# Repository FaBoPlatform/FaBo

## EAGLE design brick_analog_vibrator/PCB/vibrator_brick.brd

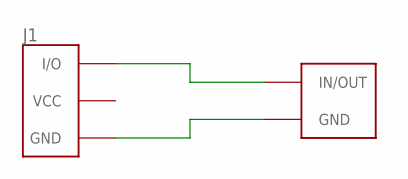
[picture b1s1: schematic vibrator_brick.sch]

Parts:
J1: BRICK_3PIN
U$1: VIBRATOR-LA3R5-480H1

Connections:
GND: J1.GND, U$1.P$2 (GND)
unnamed: J1.IN/OUT (I/O), U$1.P$1 (IN/OUT)

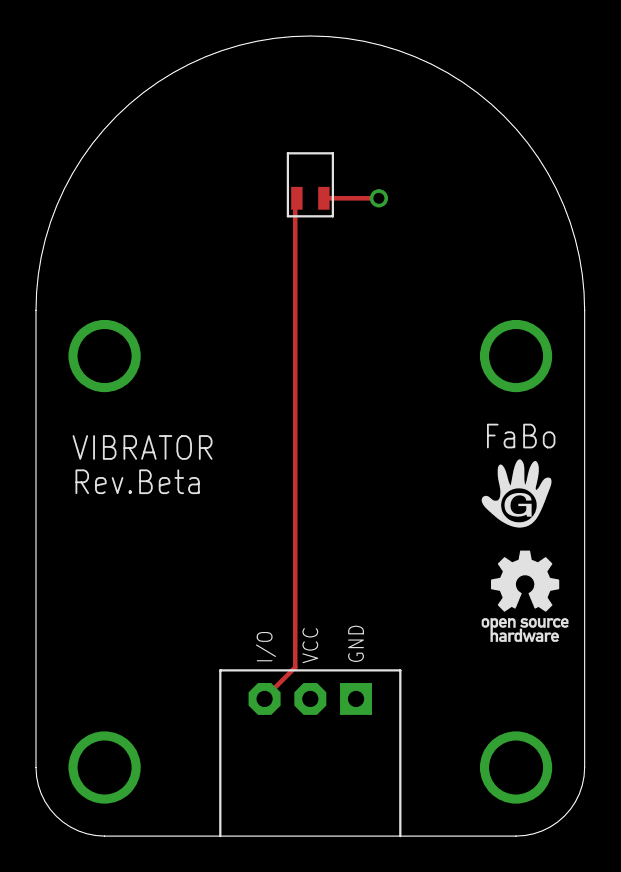
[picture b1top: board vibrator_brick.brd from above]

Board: 2 copper layers, 30.5 x 44.5 mm, 4 parts (0 on the bottom side), 2 nets.

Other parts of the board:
U$2: LOGO_GCLUE_M
U$4: LOGO_OSHW_T_M

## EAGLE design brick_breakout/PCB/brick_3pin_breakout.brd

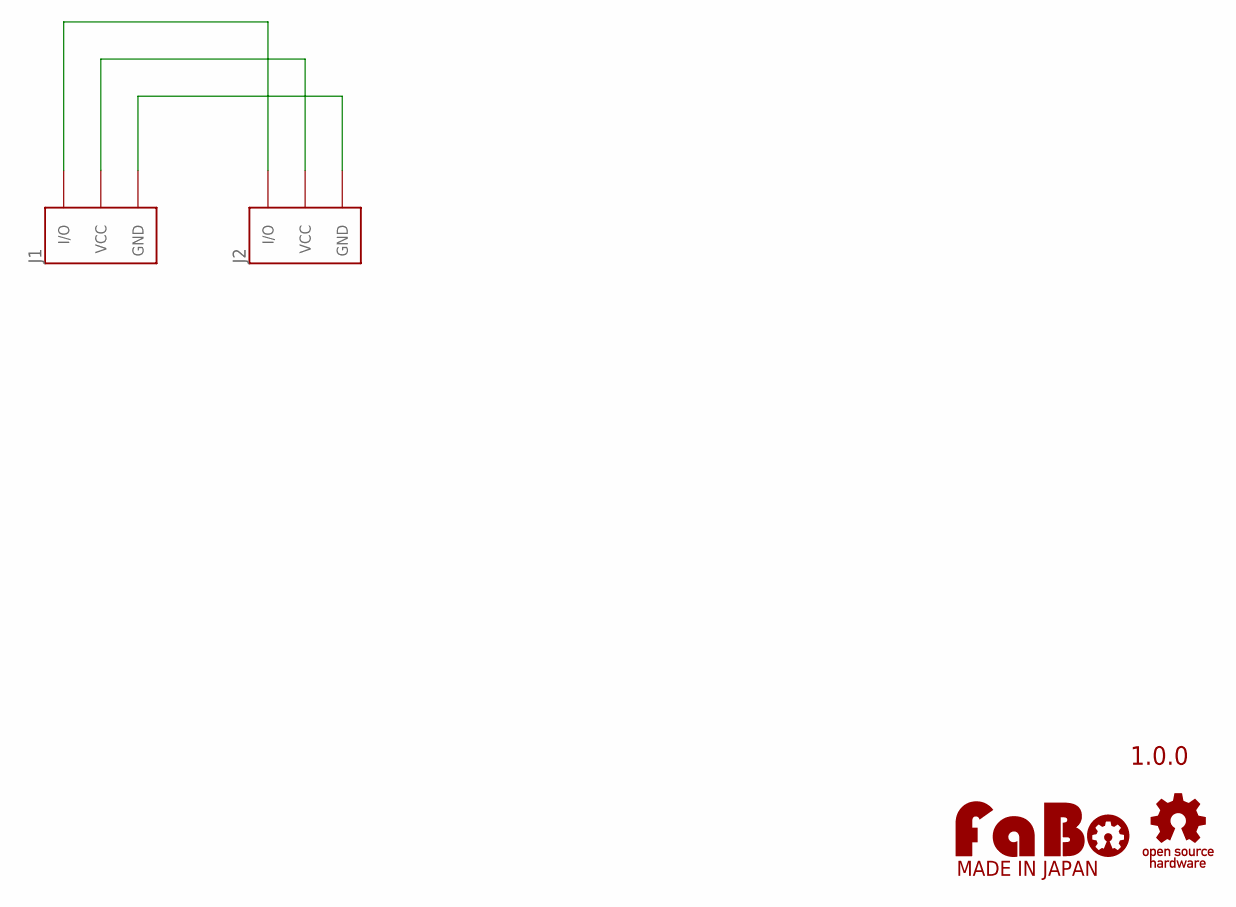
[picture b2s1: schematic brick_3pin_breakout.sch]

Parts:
J1: FABO_BRICK_3PIN-BREAKOUT; FABO_BRICK_3PIN_BREAKOUT
J2: FABO_BRICK_3PIN-CONNECTOR; FABO_BRICK_3PIN_CONNECTOR
U$2: LOGO_FABO-M_BOTTOM; LOGO_FABO_M_BOTTOM
U$3: LOGO_OSHW-T_M_BOTTOM; LOGO_OSHW_T_M_BOTTOM

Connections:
GND: J1.GND, J2.GND
IO: J1.IN/OUT (I/O), J2.IN/OUT (I/O)
VCC: J1.VCC, J2.VCC

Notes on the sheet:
1.0.0

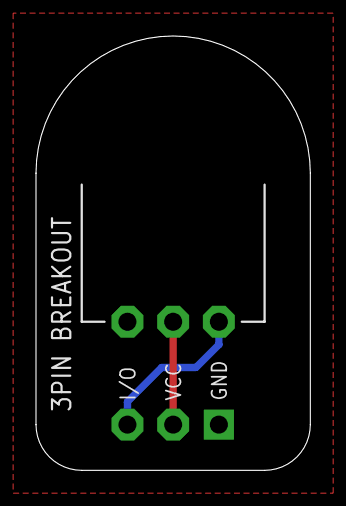
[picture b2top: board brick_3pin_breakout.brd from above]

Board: 2 copper layers, 15.2 x 24.1 mm, 4 parts (0 on the bottom side), 3 nets.

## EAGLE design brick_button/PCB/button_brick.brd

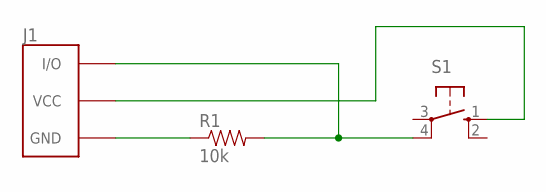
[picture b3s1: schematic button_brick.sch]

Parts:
J1: BRICK_3PIN
R1: 10k; AXIAL-0.4
S1: Button; B3F-10XX

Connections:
GND: J1.GND, R1.P$1 (1)
unnamed: J1.VCC, S1.1 (S)
unnamed: J1.IN/OUT (I/O), R1.P$2 (2), S1.4 (P1)

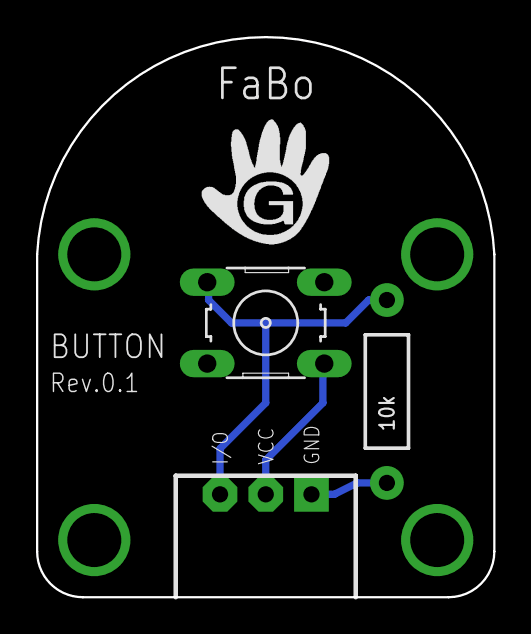
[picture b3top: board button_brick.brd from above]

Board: 2 copper layers, 25.4 x 31.1 mm, 3 parts (0 on the bottom side), 3 nets.

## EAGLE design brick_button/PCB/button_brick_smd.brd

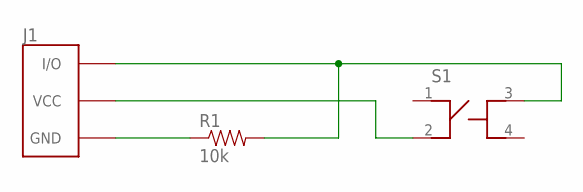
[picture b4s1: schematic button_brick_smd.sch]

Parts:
J1: BRICK_3PIN
R1: 10k; 0603-RES
S1: SWITCH-LS6J2M-T

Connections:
GND: J1.GND, R1.1
unnamed: J1.VCC, S1.2
unnamed: J1.IN/OUT (I/O), R1.2, S1.3

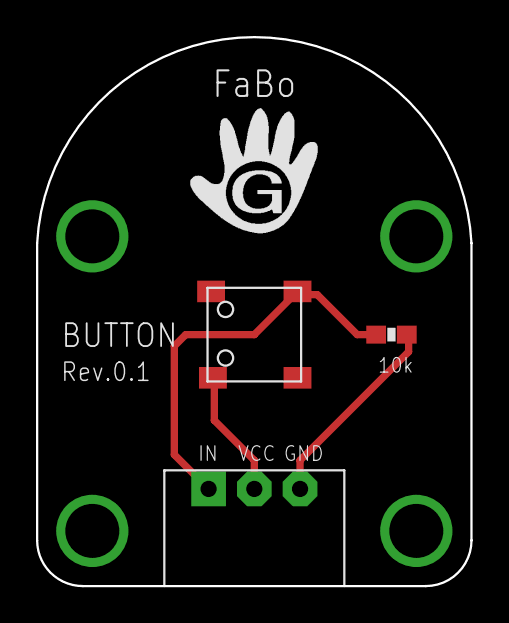
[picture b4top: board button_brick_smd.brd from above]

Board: 2 copper layers, 24.1 x 30.5 mm, 3 parts (0 on the bottom side), 3 nets.

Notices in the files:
parts and their libraries:
FaBo-Template: Released under the Creative Commons Attribution-ShareAlike 4.0 License
https://creativecommons.org/licenses/by-sa/4.0
FaBo-etc: Released under the Creative Commons
